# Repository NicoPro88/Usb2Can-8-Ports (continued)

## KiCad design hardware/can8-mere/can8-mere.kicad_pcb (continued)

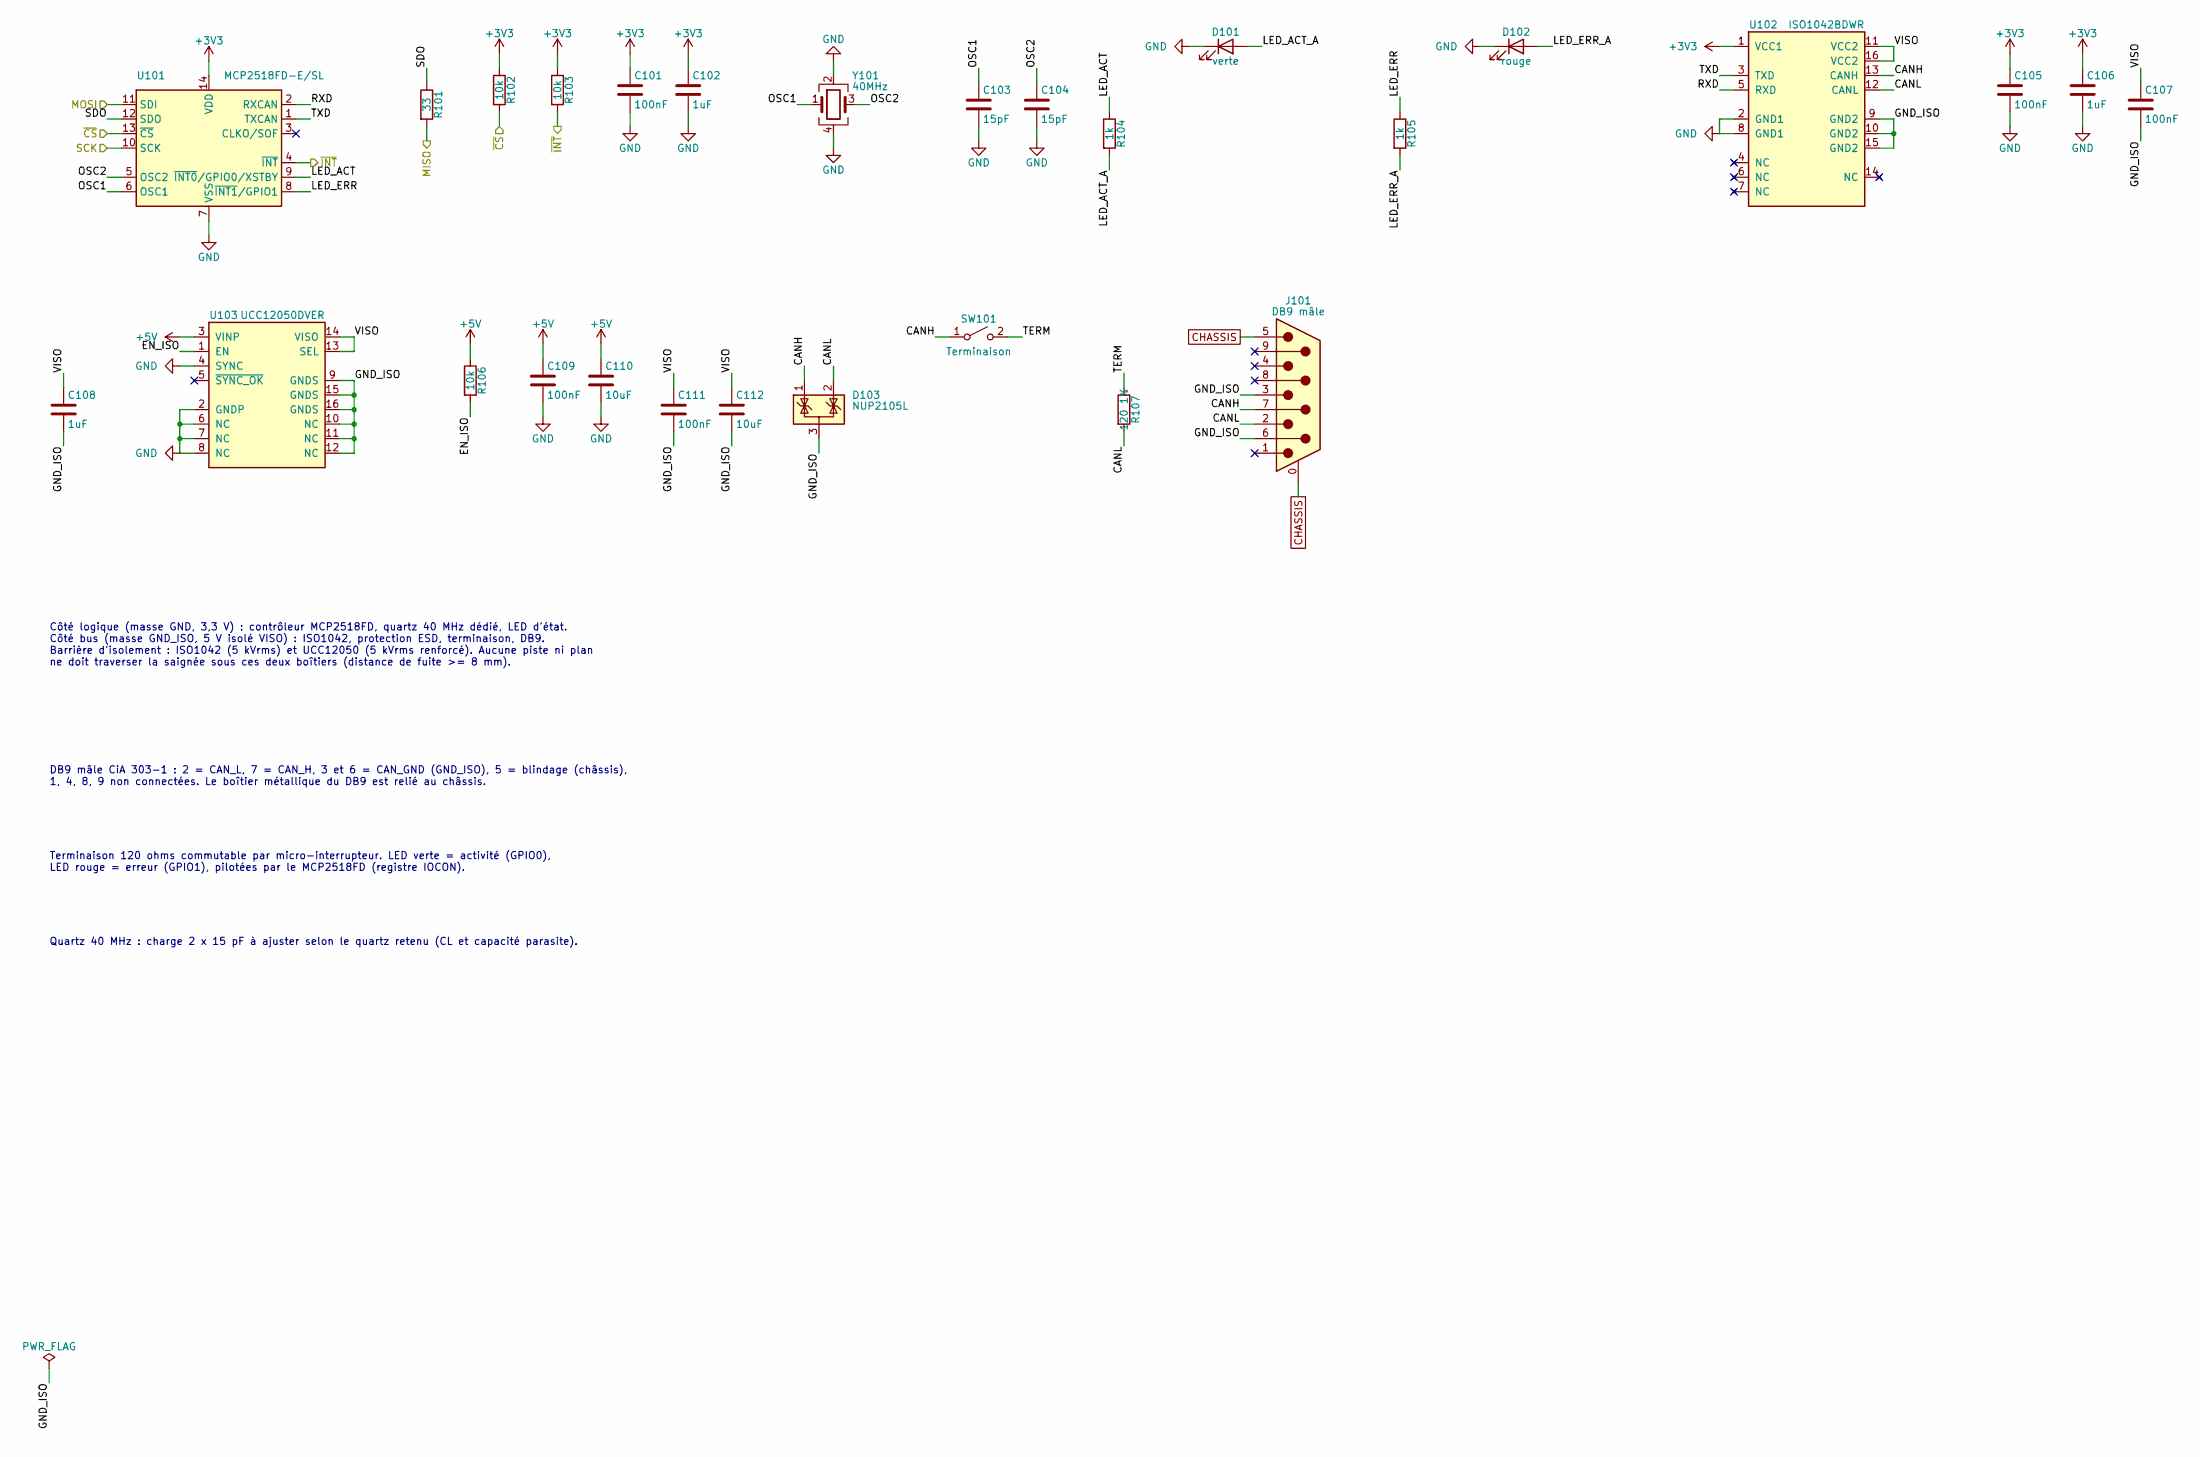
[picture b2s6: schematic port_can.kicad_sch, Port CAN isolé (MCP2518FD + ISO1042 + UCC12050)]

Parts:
C101, C105, C107, C109, C111: 100nF; C_0603_1608Metric
C102, C106, C108: 1uF; C_0805_2012Metric
C103, C104: 15pF; C_0603_1608Metric
C110, C112: 10uF; C_0805_2012Metric
D101: verte; LED_0603_1608Metric
D102: rouge; LED_0603_1608Metric
D103: NUP2105L; SOT-23
J101: DB9 mâle; DSUB-9_Pins_Horizontal_P2.77x2.84mm_EdgePinOffset9.90mm_Hou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
R101: 33; R_0603_1608Metric
R102, R103, R106: 10k; R_0603_1608Metric
R104, R105: 1k; R_0603_1608Metric
R107: 120 1%; R_1206_3216Metric
SW101: Terminaison; SW_DIP_SPSTx01_Slide_6.7x4.1mm_W8.61mm_P2.54mm_LowProfile
U101: MCP2518FD-E/SL; SOIC-14_3.9x8.7mm_P1.27mm
U102: ISO1042BDWR; SOIC-16W_7.5x10.3mm_P1.27mm
U103: UCC12050DVER; SOIC-16W_7.5x10.3mm_P1.27mm
Y101: 40MHz; Crystal_SMD_3225-4Pin_3.2x2.5mm

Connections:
+3V3: C101.1, C102.1, C105.1, C106.1, R102.1, R103.1, U101.14 (VDD), U102.1 (VCC1); also elsewhere on the board
+5V: C109.1, C110.1, R106.1, U103.3 (VINP); also elsewhere on the board
/Port CAN 1/CANH: D103.1 (K), J101.7, SW101.1 (A), U102.13 (CANH)
/Port CAN 1/CANL: D103.2 (K), J101.2, R107.2, U102.12 (CANL)
/Port CAN 1/EN_ISO: R106.2, U103.1 (EN)
/Port CAN 1/GND_ISO: C107.2, C108.2, C111.2, C112.2, D103.3 (A), J101.3, J101.6, U102.9 (GND2), U102.10 (GND2), U102.15 (GND2), U103.9 (GNDS), U103.10 (NC), U103.11 (NC), U103.12 (NC), U103.15 (GNDS), U103.16 (GNDS)
/Port CAN 1/LED_ACT: R104.1, U101.9 (~INT0/GPIO0/XSTBY)
/Port CAN 1/LED_ACT_A: D101.2 (A), R104.2
/Port CAN 1/LED_ERR: R105.1, U101.8 (~INT1/GPIO1)
/Port CAN 1/LED_ERR_A: D102.2 (A), R105.2
/Port CAN 1/OSC1: C103.1, U101.6 (OSC1), Y101.1
/Port CAN 1/OSC2: C104.1, U101.5 (OSC2), Y101.3
/Port CAN 1/RXD: U101.2 (RXCAN), U102.5 (RXD)
/Port CAN 1/SDO: R101.1, U101.12 (SDO)
/Port CAN 1/TERM: R107.1, SW101.2 (B)
/Port CAN 1/TXD: U101.1 (TXCAN), U102.3 (TXD)
/Port CAN 1/VISO: C107.1, C108.1, C111.1, C112.1, U102.11 (VCC2), U102.16 (VCC2), U103.13 (SEL), U103.14 (VISO)
CHASSIS: J101.0 (PAD), J101.5; also elsewhere on the board
GND: C101.2, C102.2, C103.2, C104.2, C105.2, C106.2, C109.2, C110.2, D101.1 (K), D102.1 (K), U101.7 (VSS), U102.2 (GND1), U102.8 (GND1), U103.2 (GNDP), U103.4 (SYNC), U103.6 (NC), U103.7 (NC), U103.8 (NC), Y101.2, Y101.4; also elsewhere on the board
SPI1_MISO: R101.2; also elsewhere on the board
SPI1_MOSI: U101.11 (SDI); also elsewhere on the board
SPI1_SCK: U101.10 (SCK); also elsewhere on the board
~CS1: R102.2, U101.13 (~CS); also elsewhere on the board
~INT1: R103.2, U101.4 (~INT); also elsewhere on the board

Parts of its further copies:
C201, C205, C207, C209, C211, C301, C305, C307, C309, C311, C401, C405, C407, C409, C411: 100nF; C_0603_1608Metric
C202, C206, C208, C302, C306, C308, C402, C406, C408: 1uF; C_0805_2012Metric
C203, C204, C303, C304, C403, C404: 15pF; C_0603_1608Metric
C210, C212, C310, C312, C410, C412: 10uF; C_0805_2012Metric
D201, D301, D401: verte; LED_0603_1608Metric
D202, D302, D402: rouge; LED_0603_1608Metric
D203, D303, D403: NUP2105L; SOT-23
J201, J301, J401: DB9 mâle; DSUB-9_Pins_Horizontal_P2.77x2.84mm_EdgePinOffset9.90mm_Hou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
R201, R301, R401: 33; R_0603_1608Metric
R202, R203, R206, R302, R303, R306, R402, R403, R406: 10k; R_0603_1608Metric
R204, R205, R304, R305, R404, R405: 1k; R_0603_1608Metric
R207, R307, R407: 120 1%; R_1206_3216Metric
SW201, SW301, SW401: Terminaison; SW_DIP_SPSTx01_Slide_6.7x4.1mm_W8.61mm_P2.54mm_LowProfile
U201, U301, U401: MCP2518FD-E/SL; SOIC-14_3.9x8.7mm_P1.27mm
U202, U302, U402: ISO1042BDWR; SOIC-16W_7.5x10.3mm_P1.27mm
U203, U303, U403: UCC12050DVER; SOIC-16W_7.5x10.3mm_P1.27mm
Y201, Y301, Y401: 40MHz; Crystal_SMD_3225-4Pin_3.2x2.5mm

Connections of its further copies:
+3V3: C201.1, C202.1, C205.1, C206.1, C301.1, C302.1, C305.1, C306.1, C401.1, C402.1, C405.1, C406.1, R202.1, R203.1, R302.1, R303.1, R402.1, R403.1, U201.14 (VDD), U202.1 (VCC1), U301.14 (VDD), U302.1 (VCC1), U401.14 (VDD), U402.1 (VCC1); also elsewhere on the board
+5V: C209.1, C210.1, C309.1, C310.1, C409.1, C410.1, R206.1, R306.1, R406.1, U203.3 (VINP), U303.3 (VINP), U403.3 (VINP); also elsewhere on the board
/Port CAN 2/CANH: D203.1 (K), J201.7, SW201.1 (A), U202.13 (CANH)
/Port CAN 2/CANL: D203.2 (K), J201.2, R207.2, U202.12 (CANL)
/Port CAN 2/EN_ISO: R206.2, U203.1 (EN)
/Port CAN 2/GND_ISO: C207.2, C208.2, C211.2, C212.2, D203.3 (A), J201.3, J201.6, U202.9 (GND2), U202.10 (GND2), U202.15 (GND2), U203.9 (GNDS), U203.10 (NC), U203.11 (NC), U203.12 (NC), U203.15 (GNDS), U203.16 (GNDS)
/Port CAN 2/LED_ACT: R204.1, U201.9 (~INT0/GPIO0/XSTBY)
/Port CAN 2/LED_ACT_A: D201.2 (A), R204.2
/Port CAN 2/LED_ERR: R205.1, U201.8 (~INT1/GPIO1)
/Port CAN 2/LED_ERR_A: D202.2 (A), R205.2
/Port CAN 2/OSC1: C203.1, U201.6 (OSC1), Y201.1
/Port CAN 2/OSC2: C204.1, U201.5 (OSC2), Y201.3
/Port CAN 2/RXD: U201.2 (RXCAN), U202.5 (RXD)
/Port CAN 2/SDO: R201.1, U201.12 (SDO)
/Port CAN 2/TERM: R207.1, SW201.2 (B)
/Port CAN 2/TXD: U201.1 (TXCAN), U202.3 (TXD)
/Port CAN 2/VISO: C207.1, C208.1, C211.1, C212.1, U202.11 (VCC2), U202.16 (VCC2), U203.13 (SEL), U203.14 (VISO)
/Port CAN 3/CANH: D303.1 (K), J301.7, SW301.1 (A), U302.13 (CANH)
/Port CAN 3/CANL: D303.2 (K), J301.2, R307.2, U302.12 (CANL)
/Port CAN 3/EN_ISO: R306.2, U303.1 (EN)
/Port CAN 3/GND_ISO: C307.2, C308.2, C311.2, C312.2, D303.3 (A), J301.3, J301.6, U302.9 (GND2), U302.10 (GND2), U302.15 (GND2), U303.9 (GNDS), U303.10 (NC), U303.11 (NC), U303.12 (NC), U303.15 (GNDS), U303.16 (GNDS)
/Port CAN 3/LED_ACT: R304.1, U301.9 (~INT0/GPIO0/XSTBY)
/Port CAN 3/LED_ACT_A: D301.2 (A), R304.2
/Port CAN 3/LED_ERR: R305.1, U301.8 (~INT1/GPIO1)
/Port CAN 3/LED_ERR_A: D302.2 (A), R305.2
/Port CAN 3/OSC1: C303.1, U301.6 (OSC1), Y301.1
/Port CAN 3/OSC2: C304.1, U301.5 (OSC2), Y301.3
/Port CAN 3/RXD: U301.2 (RXCAN), U302.5 (RXD)
/Port CAN 3/SDO: R301.1, U301.12 (SDO)
/Port CAN 3/TERM: R307.1, SW301.2 (B)
/Port CAN 3/TXD: U301.1 (TXCAN), U302.3 (TXD)
/Port CAN 3/VISO: C307.1, C308.1, C311.1, C312.1, U302.11 (VCC2), U302.16 (VCC2), U303.13 (SEL), U303.14 (VISO)
/Port CAN 4/CANH: D403.1 (K), J401.7, SW401.1 (A), U402.13 (CANH)
/Port CAN 4/CANL: D403.2 (K), J401.2, R407.2, U402.12 (CANL)
/Port CAN 4/EN_ISO: R406.2, U403.1 (EN)
/Port CAN 4/GND_ISO: C407.2, C408.2, C411.2, C412.2, D403.3 (A), J401.3, J401.6, U402.9 (GND2), U402.10 (GND2), U402.15 (GND2), U403.9 (GNDS), U403.10 (NC), U403.11 (NC), U403.12 (NC), U403.15 (GNDS), U403.16 (GNDS)
/Port CAN 4/LED_ACT: R404.1, U401.9 (~INT0/GPIO0/XSTBY)
/Port CAN 4/LED_ACT_A: D401.2 (A), R404.2
/Port CAN 4/LED_ERR: R405.1, U401.8 (~INT1/GPIO1)
/Port CAN 4/LED_ERR_A: D402.2 (A), R405.2
/Port CAN 4/OSC1: C403.1, U401.6 (OSC1), Y401.1
/Port CAN 4/OSC2: C404.1, U401.5 (OSC2), Y401.3
/Port CAN 4/RXD: U401.2 (RXCAN), U402.5 (RXD)
/Port CAN 4/SDO: R401.1, U401.12 (SDO)
/Port CAN 4/TERM: R407.1, SW401.2 (B)
/Port CAN 4/TXD: U401.1 (TXCAN), U402.3 (TXD)
/Port CAN 4/VISO: C407.1, C408.1, C411.1, C412.1, U402.11 (VCC2), U402.16 (VCC2), U403.13 (SEL), U403.14 (VISO)
CHASSIS: J201.0 (PAD), J201.5, J301.0 (PAD), J301.5, J401.0 (PAD), J401.5; also elsewhere on the board
GND: C201.2, C202.2, C203.2, C204.2, C205.2, C206.2, C209.2, C210.2, C301.2, C302.2, C303.2, C304.2, C305.2, C306.2, C309.2, C310.2, C401.2, C402.2, C403.2, C404.2, C405.2, C406.2, C409.2, C410.2, D201.1 (K), D202.1 (K), D301.1 (K), D302.1 (K), D401.1 (K), D402.1 (K), U201.7 (VSS), U202.2 (GND1), U202.8 (GND1), U203.2 (GNDP), U203.4 (SYNC), U203.6 (NC), U203.7 (NC), U203.8 (NC), U301.7 (VSS), U302.2 (GND1), U302.8 (GND1), U303.2 (GNDP), U303.4 (SYNC), U303.6 (NC), U303.7 (NC), U303.8 (NC), U401.7 (VSS), U402.2 (GND1), U402.8 (GND1), U403.2 (GNDP), U403.4 (SYNC), U403.6 (NC), U403.7 (NC), U403.8 (NC), Y201.2, Y201.4, Y301.2, Y301.4, Y401.2, Y401.4; also elsewhere on the board
SPI1_MISO: R201.2; also elsewhere on the board
SPI1_MOSI: U201.11 (SDI); also elsewhere on the board
SPI1_SCK: U201.10 (SCK); also elsewhere on the board
SPI2_MISO: R301.2, R401.2; also elsewhere on the board
SPI2_MOSI: U301.11 (SDI), U401.11 (SDI); also elsewhere on the board
SPI2_SCK: U301.10 (SCK), U401.10 (SCK); also elsewhere on the board
~CS2: R202.2, U201.13 (~CS); also elsewhere on the board
~CS3: R302.2, U301.13 (~CS); also elsewhere on the board
~CS4: R402.2, U401.13 (~CS); also elsewhere on the board
~INT2: R203.2, U201.4 (~INT); also elsewhere on the board
~INT3: R303.2, U301.4 (~INT); also elsewhere on the board
~INT4: R403.2, U401.4 (~INT); also elsewhere on the board

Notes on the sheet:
Côté logique (masse GND, 3,3 V) : contrôleur MCP2518FD, quartz 40 MHz dédié, LED d'état. Côté bus (masse GND_ISO, 5 V isolé VISO) : ISO1042, protection ESD, terminaison, DB9. Barrière d'isolement : ISO1042 (5 kVrms) et UCC12050 (5 kVrms renforcé). Aucune piste ni plan ne doit traverser la saignée s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
DB9 mâle CiA 303-1 : 2 = CAN_L, 7 = CAN_H, 3 et 6 = CAN_GND (GND_ISO), 5 = blindage (châssis), 1, 4, 8, 9 non connectées. Le boîtier métallique du DB9 est relié au châssis.
Terminaison 120 ohms commutable par micro-interrupteur. LED verte = activité (GPIO0), LED rouge = erreur (GPIO1), pilotées par le MCP2518FD (registre IOCON).
Quartz 40 MHz : charge 2 x 15 pF à ajuster selon le quartz retenu (CL et capacité parasite).

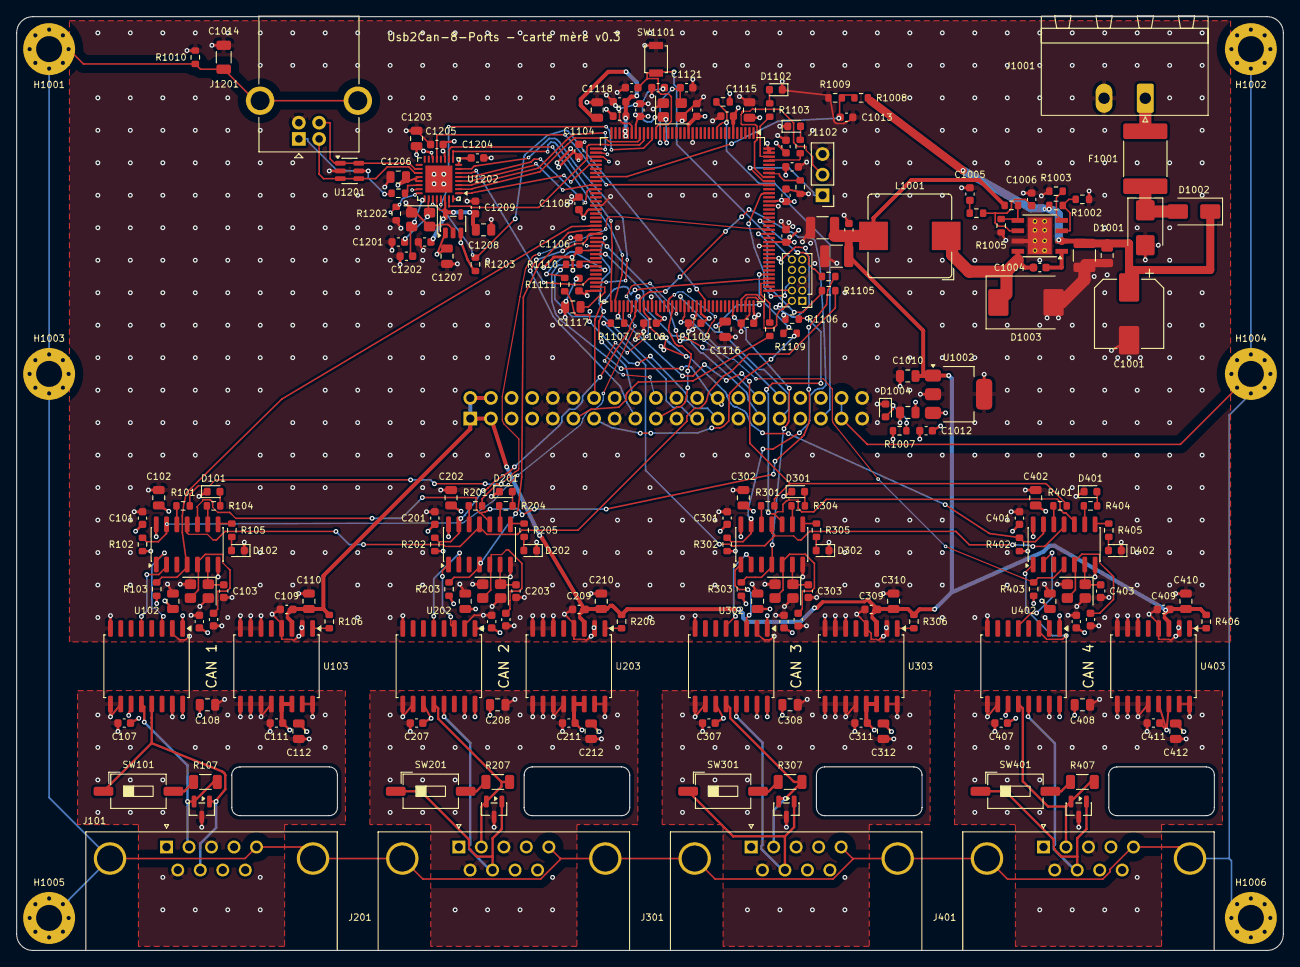
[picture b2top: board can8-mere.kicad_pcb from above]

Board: 4 copper layers, 156.0 x 115.0 mm, 212 parts (1 on the bottom side), 150 nets.

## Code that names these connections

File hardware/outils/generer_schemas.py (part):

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                   'ne doit traverser la saignée sous ces deux boîtiers (distance de fuite >= 8 mm).',
                   'DB9 mâle CiA 303-1 : 2 = CAN_L, 7 = CAN_H, 3 et 6 = CAN_GND (GND_ISO), 5 = blindage (châssis),\n'
                   '1, 4, 8, 9 non connectées. Le boîtier métallique du DB9 est relié au châssis.',
                   'Terminaison 120 ohms commutable par micro-interrupteur. LED verte = activité (GPIO0),\n'
                   'LED rouge = erreur (GPIO1), pilotées par le MCP2518FD (registre IOCON).',
                   'Quartz 40 MHz : charge 2 x 15 pF à ajuster selon le quartz retenu (CL et capacité parasite).',
               ])
    sh.pwr_flags = ['GND_ISO']
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    # chip-selects et interruptions
    78: '~{CS1}', 79: '~{CS2}', 80: '~{CS3}', 81: '~{CS4}',
    58: '~{CS5}', 59: '~{CS6}', 60: '~{CS7}', 63: '~{CS8}',
    # ~INT1 et ~INT2 (ports 1 et 2, à gauche) sur PG0 / PG1, côté gauche du boîtier ; ~INT3 sur PA11,
    # sous le boîtier près du port 3 : la rangée du bas, vers le connecteur carte à carte, est saturée
    56: '~{INT1}', 57: '~{INT2}', 103: '~{INT3}', 87: '~{INT4}',
    88: '~{INT5}', 89: '~{INT6}', 90: '~{INT7}', 91: '~{INT8}',
}
ULPI_PINS = {41: 'ULPI_CLK', 26: 'ULPI_STP', 28: 'ULPI_DIR', 29: 'ULPI_NXT', 37: 'ULPI_D0',
             46: 'ULPI_D1', 47: 'ULPI_D2', 69: 'ULPI_D3', 70: 'ULPI_D4', 73: 'ULPI_D5',
             74: 'ULPI_D6', 135: 'ULPI_D7', 96: '~{ULPI_RST}'}
MISC_PINS = {105: 'SWDIO', 109: 'SWCLK', 133: 'SWO', 136: 'DBG_TX', 137: 'DBG_RX',
             141: 'LED_ETAT', 142: 'LED_ERREUR', 44: 'VIN_MES', 10: '~{FILLE_PRESENTE}',
             23: 'HSE_IN', 24: 'HSE_OUT', 25: 'NRST', 138: 'BOOT0'}
GLOBAL_MERE = ({'VIN_MES', 'CHASSIS', '~{FILLE_PRESENTE}', '+VIN', '~{ULPI_RST}'}
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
